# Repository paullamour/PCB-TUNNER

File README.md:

# PCB TUNNER

This is a Printed Circuit Board guitar tunner.

## Overview

Select the target note using the OLED display and the push buttons. PCB Tuner listens to the guitar signal through a digital MEMS microphone, detects pitch on an ESP32-S3, and shows the result through a row of LEDs, arranged from the lowest to the highest pitch, left to right. The middle LED turns green when the string is correctly tuned. The board runs off a small LiPo battery and charges over USB-C.

The device is not intended to be used while charging (no power-path/load-sharing circuitry).

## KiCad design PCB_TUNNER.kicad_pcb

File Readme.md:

# PCB TUNNER

This is a Printed Circuit Board guitar tunner.

## Overview

Select the target note using the OLED display and the push buttons. PCB Tuner listens to the guitar signal through a digital MEMS microphone, detects pitch on an ESP32-S3, and shows the result through a row of LEDs, arranged from the lowest to the highest pitch, left to right. The middle LED turns green when the string is correctly tuned. The board runs off a small LiPo battery and charges over USB-C.

The device is not intended to be used while charging (no power-path/load-sharing circuitry).

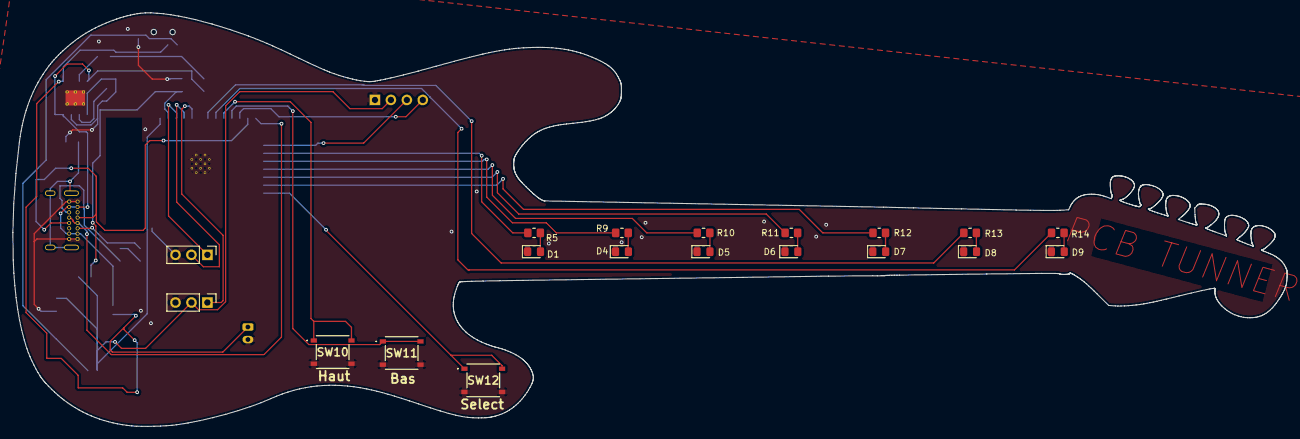
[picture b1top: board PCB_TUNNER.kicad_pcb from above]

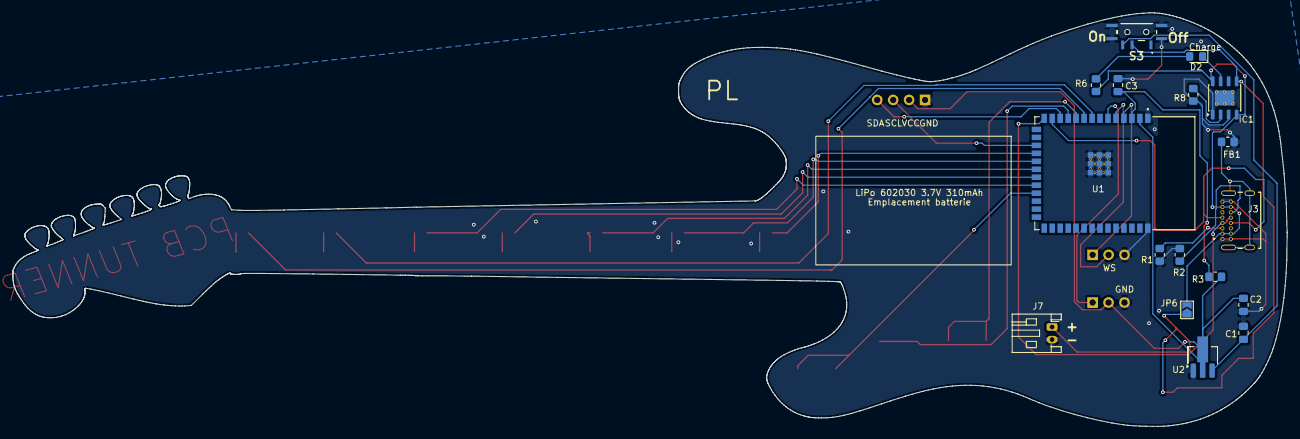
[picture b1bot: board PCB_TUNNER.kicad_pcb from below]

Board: 2 copper layers, 203.0 x 65.9 mm, 38 parts (17 on the bottom side), 36 nets.

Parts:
 LiPo 602030 3.7V 310mAh: Emplacement batterie; Sans titre
C1, C2: 22u; C_0805_2012Metric_Pad1.18x1.45mm_HandSolder
C3: 1u; C_0805_2012Metric_Pad1.18x1.45mm_HandSolder
D1, D2, D4, D5, D6, D7, D8, D9: LED; D_0805_2012Metric_Pad1.15x1.40mm_HandSolder
FB1: FerriteBead; R_0805_2012Metric_Pad1.20x1.40mm_HandSolder
GND: Conn_01x03_Pin; PinHeader_1x03_P2.54mm_Vertical
IC1: DIO5508XS8; HSOP-8-1EP_3.9x4.9mm_P1.27mm_EP2.41x3.1mm_ThermalVias
J3: USB4085-GF-A_REVB; GCT_USB4085-GF-A_REVA4
J7: Conn_01x02; JST_PH_S2B-PH-K_1x02_P2.00mm_Horizontal
JP6: SolderJumper_2_Open; SolderJumper-2_P1.3mm_Open_TrianglePad1.0x1.5mm
R1, R2: 5.1K; R_0805_2012Metric_Pad1.20x1.40mm_HandSolder
R3, R6: 10K; R_0805_2012Metric_Pad1.20x1.40mm_HandSolder
R5, R9, R10, R11, R12, R13, R14: 330; R_0805_2012Metric_Pad1.20x1.40mm_HandSolder
R8: 2K; R_0805_2012Metric_Pad1.20x1.40mm_HandSolder
S3: MSK12C02
SW10, SW11, SW12: PTS526_SK15_SMTR2_LFS; PTS526SK15SMTR2LFS
U1: ESP32-S3-WROOM-1-N8; XCVR_ESP32-S3-WROOM-1-N8
U2: AZ1117CR-3.3TRG1; SOT-89-3_Handsoldering
U3: ER_OLEDM0.91_1x-I2C; SSD1306_module
WS: Conn_01x03_Pin; PinHeader_1x03_P2.54mm_Vertical

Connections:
+3.3V: C2.1, GND.2, R3.2, U1.2 (3V3_2), U2.2 (VO), U3.2 (VCC)
+BATT: IC1.5 (BAT), J7.1, JP6.1 (A), S3.B1 (COM)
+BATT_after_switch: C1.1, S3.C1 (NO), U2.3 (VI)
/Charge: D2.1 (K), IC1.7 (CHRGB)
/D+: J3.A6 (DP1), J3.B6 (DP2), U1.14 (IO20_14)
/D-: J3.A7 (DN1), J3.B7 (DN2), U1.13 (IO19_13)
BAS: SW11.1, SW11.2, U1.11 (IO18_11)
GND: C1.2, C2.2, C3.2, D1.1 (K), D4.1 (K), D5.1 (K), D6.1 (K), D7.1 (K), D8.1 (K), D9.1 (K), FB1.2, GND.3, IC1.1 (TEMP), IC1.3 (GND), IC1.9 (EP), J3.A1 (GND), J3.A12 (GND), J3.B1 (GND), J3.B12 (GND), J7.2, R1.1, R2.2, R8.1, S3.MP1, S3.MP2, S3.MP3, S3.MP4, SW10.3, SW10.4, SW11.3, SW11.4, SW12.3, SW12.4, U1.1 (GND_1), U1.40 (GND_40), U1.41 (GND_41_9), U2.1 (GND), U3.1 (GND), WS.3
HAUT: SW10.1, SW10.2, U1.10 (IO17_10)
LED_1: R5.1, U1.18 (IO10_18)
LED_2: R9.1, U1.19 (IO11_19)
LED_3: R10.1, U1.20 (IO12_20)
LED_4: R11.1, U1.21 (IO13_21)
LED_5: R12.1, U1.22 (IO14_22)
LED_6: R13.1, U1.8 (IO15_8)
LED_7: R14.1, U1.9 (IO16_9)
unnamed: D1.2 (A), R5.2
unnamed: D2.2 (A), R6.2
unnamed: D4.2 (A), R9.2
unnamed: D5.2 (A), R10.2
unnamed: D6.2 (A), R11.2
unnamed: D7.2 (A), R12.2
unnamed: D8.2 (A), R13.2
unnamed: D9.2 (A), R14.2
unnamed: FB1.1, J3.S1 (SHELL), J3.S2 (SHELL), J3.S3 (SHELL), J3.S4 (SHELL)
unnamed: IC1.2 (PROG), R8.2
unnamed: J3.A5 (CC1), R1.2
unnamed: J3.B5 (CC2), R2.1
unnamed: C3.1, R3.1, U1.3 (EN_3)
SCK: U1.4 (IO4_4), WS.1
SCL: U1.17 (IO9_17), U3.3 (SCL)
SD: GND.1, U1.6 (IO6_6)
SDA: U1.12 (IO8_12), U3.4 (SDA)
SELECTIONER: SW12.1, SW12.2, U1.23 (IO21_23)
VBUS: IC1.4 (VCC), IC1.8 (CE), J3.A4 (VBUS), J3.A9 (VBUS), J3.B4 (VBUS), J3.B9 (VBUS), JP6.2 (B), R6.1
WS: U1.5 (IO5_5), WS.2
